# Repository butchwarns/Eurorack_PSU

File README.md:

# Eurorack PSU

A simple linear adjustable power supply for modular synthesizers in the Eurorack format.  
It's easy to build and outputs more than 1A at +12V, -12V and +5V each.

*Eurorack_PSU v0.1.0*

## Motivation

I designed this power supply for use in my own modular synthesizer projects. Thought i'd share the board with other synth builders.
(Gerber files in the repo can be directly uploaded to your pcb manufacturer of choice. Interactive BOM for easy assembly included.)

## A few words of caution

**DANGER OF DEATH:** Do not attempt to build this project if you do not fully know what you are doing!!!  
The build requires wiring a transformer to mains voltage, which can easily end in a deadly accident if done incorrectly!  

**CAUTION:** This project is not suited for beginners! Use the files in this repository at your own risk!  

<hr style="border:1px solid gray">

If you do know what you are doing and want to build the PSU:

I will do my best to test everything, but the occasional bug might still find its way into the project files. Don't hesitate to report found bugs or share ideas on how to improve the board.

## Project status

The *main* branch of this repository holds the current tested version of the board. All potentially breaking changes will be done on the *develop* branch and the build will be tested before merging. Images in this README do not necessarily show the most recent version of the board, though all images will have version numbers in their title.  

## Tech/framework used

- KiCad

## Features

- For standard +12V, -12V, +5V power (±15V should also be possible by adjusting the potentiometers but was not yet tested).  
- $\approx 1.3A$ per rail (regulators are rated $1.5A$ abolute maximum)
- Three LEDs indicate the rails being powered.
- Little heat generation
- Fuses on both secondary windings

Designed to work with the [Eurorack_Bus_Board](https://github.com/butchwarns/Eurorack_Bus_Board/), but can also be used in conjunction with other bus boards.

## Installation

M3 screws and PCB spacers can be used to mount the board to the back of a case.  
Regular 6.3mm flat connectors are used for connecting to both transformer and bus board.  

Use a toroidal transformer with split secondaries at 15VAC and choose one capable of driving enough current to meet your needs!  
(Both positive rails are powered by the same transformer winding.)

## How to use?

Both secondary windings of the transformer are connected on one side of the board. Eurorack power is output on the other side.  
Use a voltmeter to adjust the individual voltages by turning the trimmer potentiometers. if you wan't to be extra precise you can attach a suitable load resistance and adjust the voltages when drawing the same amount of current your modules would do.

## How to build?

Upload the *.zip* in the `gerber_files/` folder to your PCB manufacturer's website to order.

An interactive HTML BOM is available in the `bom/` folder. Just open it in a browser and tick off sourced/placed components.  
Also shows where on the board components should be placed.  

**HINT:** Use good quality solder/flux and clean the board thoroughly after soldering!  

## Component availability/choices

No unobtainium in this project. All components should be easily sourced, at least in europe.  
Feel free to recommend more easily available parts if you can think of any worth replacing.

## Contact

Any questions?   

🡢 contact[at]butchwarns.de

## License

*(TODO: Find appropriate open-hardware license!)*

> Until otherwise stated here, the project is default licensed as proprietary.

Build as many of these boards as you want for personal use, but please make it obvious if your build has modified the project files in any way to avoid confusion!  

My name and any logo of mine that might be present on the board design are copyrighted and are not free to use.

You are free to share the images in the `pictures/` folder of this repository with correct attribution or a link to the project.  

Copr. 2021, Butch Warns

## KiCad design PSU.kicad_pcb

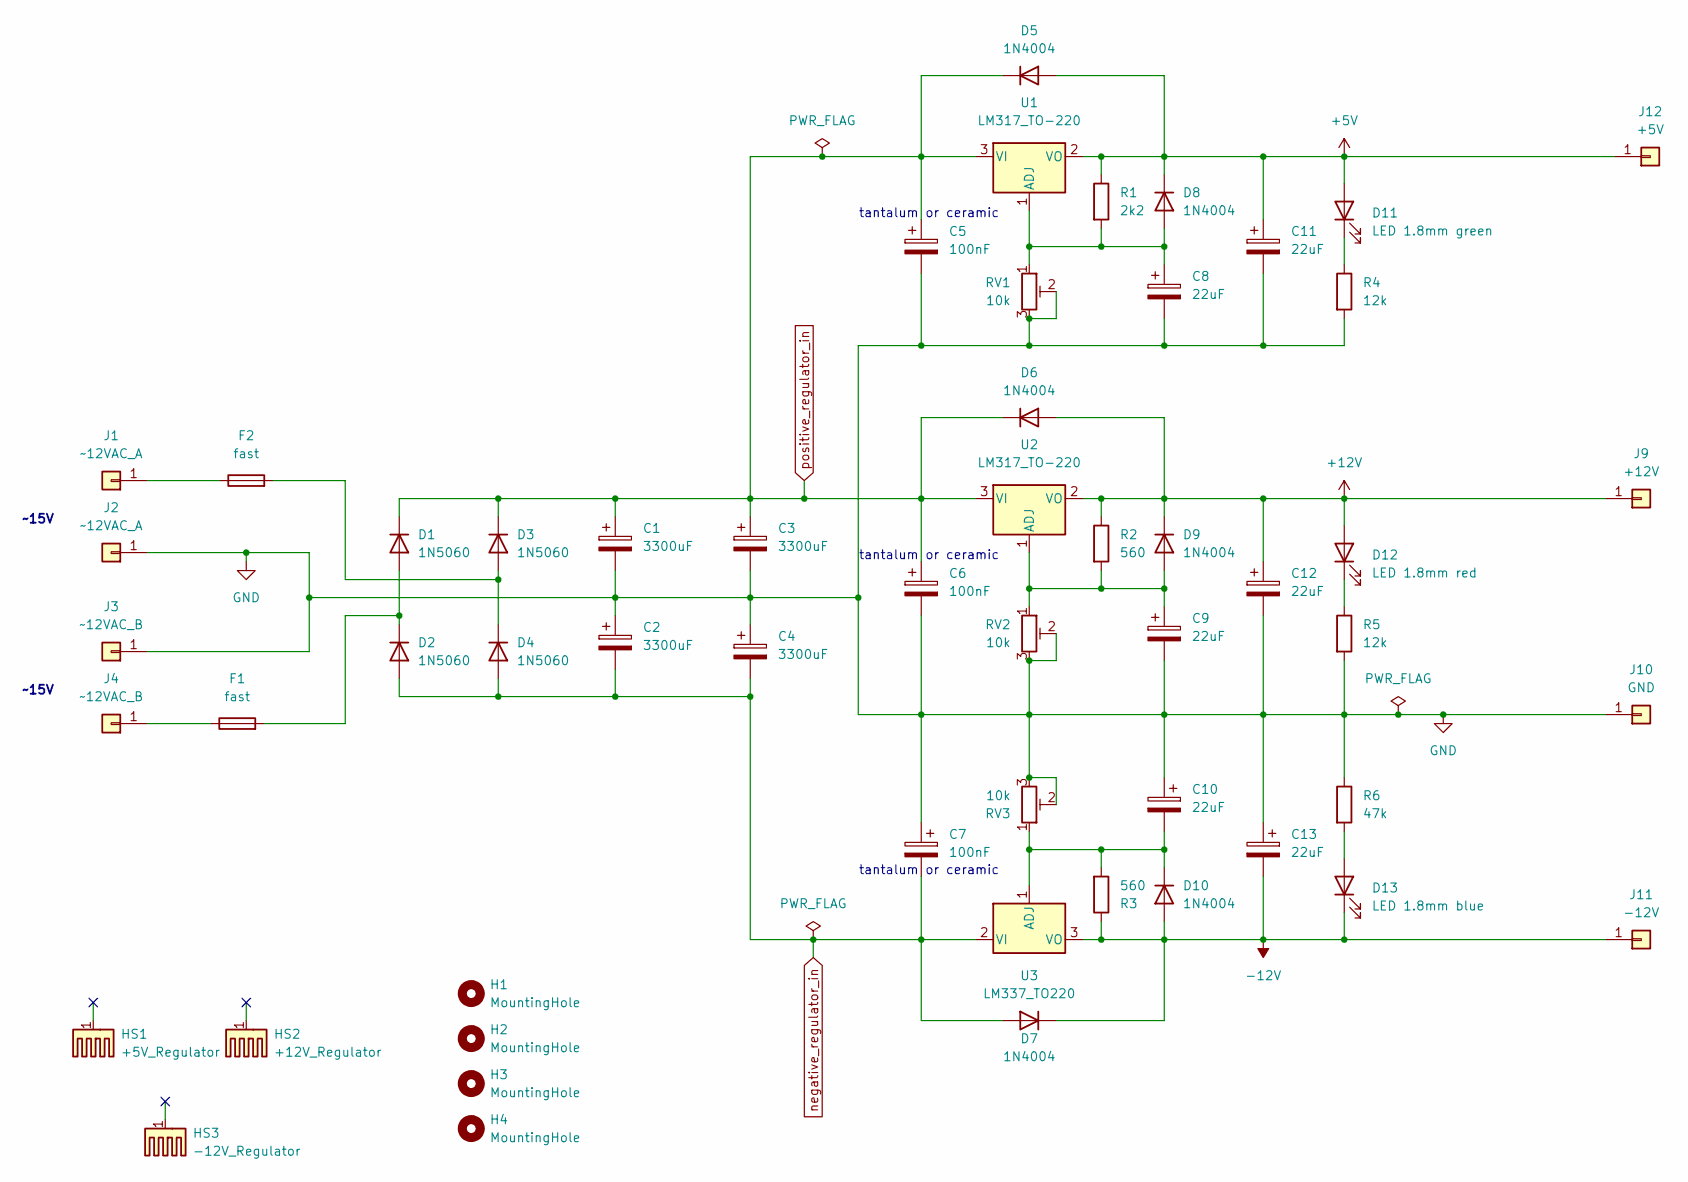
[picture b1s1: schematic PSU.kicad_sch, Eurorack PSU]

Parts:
C1, C2, C3, C4: 3300uF; CP_Radial_D16.0mm_P7.50mm
C5, C6, C7: 100nF; C_Disc_D3.0mm_W1.6mm_P2.50mm
C8, C9, C10, C11, C12, C13: 22uF; CP_Radial_D5.0mm_P2.00mm
D1, D2, D3, D4: 1N5060; D_DO-15_P10.16mm_Horizontal
D5, D6, D7, D8, D9, D10: 1N4004; D_DO-41_SOD81_P10.16mm_Horizontal
D11: LED 1.8mm green; LED_D3.0mm
D12: LED 1.8mm red; LED_D3.0mm
D13: LED 1.8mm blue; LED_D3.0mm
F1, F2: fast; Fuseholder_Cylinder-5x20mm_Schurter_0031_8201_Horizontal_Op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
H1, H2, H3, H4: MountingHole; MountingHole_3.2mm_M3
HS1: +5V_Regulator; Heatsink_Fischer_SK129-STS_42x25mm_2xDrill2.5mm
HS2: +12V_Regulator; Heatsink_Fischer_SK129-STS_42x25mm_2xDrill2.5mm
HS3: -12V_Regulator; Heatsink_Fischer_SK129-STS_42x25mm_2xDrill2.5mm
J1, J2: ~12VAC_A; Flat_Connector_Vogt_6.35mm_P5mm
J3, J4: ~12VAC_B; Flat_Connector_Vogt_6.35mm_P5mm
J9: +12V; Flat_Connector_Vogt_6.35mm_P5mm
J10: GND; Flat_Connector_Vogt_6.35mm_P5mm
J11: -12V; Flat_Connector_Vogt_6.35mm_P5mm
J12: +5V; Flat_Connector_Vogt_6.35mm_P5mm
R1: 2k2; R_Axial_DIN0207_L6.3mm_D2.5mm_P7.62mm_Horizontal
R2, R3: 560; R_Axial_DIN0207_L6.3mm_D2.5mm_P7.62mm_Horizontal
R4, R5: 12k; R_Axial_DIN0207_L6.3mm_D2.5mm_P7.62mm_Horizontal
R6: 47k; R_Axial_DIN0207_L6.3mm_D2.5mm_P7.62mm_Horizontal
RV1, RV2, RV3: 10k; Potentiometer_Bourns_3296W_Vertical
U1, U2: LM317_TO-220; TO-220-3_Vertical
U3: LM337_TO220; TO-220-3_Vertical

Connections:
+5V: C11.1, D5.2 (A), D8.1 (K), D11.2 (A), J12.1, R1.1, U1.2 (VO)
+12V: C12.1, D6.2 (A), D9.1 (K), D12.2 (A), J9.1, R2.1, U2.2 (VO)
-12V: C13.2, D7.1 (K), D10.2 (A), D13.1 (K), J11.1, R3.1, U3.3 (VO)
GND: C1.2, C2.1, C3.2, C4.1, C5.2, C6.2, C7.1, C8.2, C9.2, C10.1, C11.2, C12.2, C13.1, J2.1, J3.1, J10.1, R4.2, R5.2, R6.1, RV1.2, RV1.3, RV2.2, RV2.3, RV3.2, RV3.3
unnamed: C8.1, D8.2 (A), R1.2, RV1.1, U1.1 (ADJ)
unnamed: C9.1, D9.2 (A), R2.2, RV2.1, U2.1 (ADJ)
unnamed: C10.2, D10.1 (K), R3.2, RV3.1, U3.1 (ADJ)
unnamed: D1.2 (A), D2.1 (K), F1.2
unnamed: D3.2 (A), D4.1 (K), F2.2
unnamed: D11.1 (K), R4.1
unnamed: D12.1 (K), R5.1
unnamed: D13.2 (A), R6.2
unnamed: F1.1, J4.1
unnamed: F2.1, J1.1
negative_regulator_in: C2.2, C4.2, C7.2, D2.2 (A), D4.2 (A), D7.2 (A), U3.2 (VI)
positive_regulator_in: C1.1, C3.1, C5.1, C6.1, D1.1 (K), D3.1 (K), D5.1 (K), D6.1 (K), U1.3 (VI), U2.3 (VI)

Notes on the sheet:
tantalum or ceramic
~15V

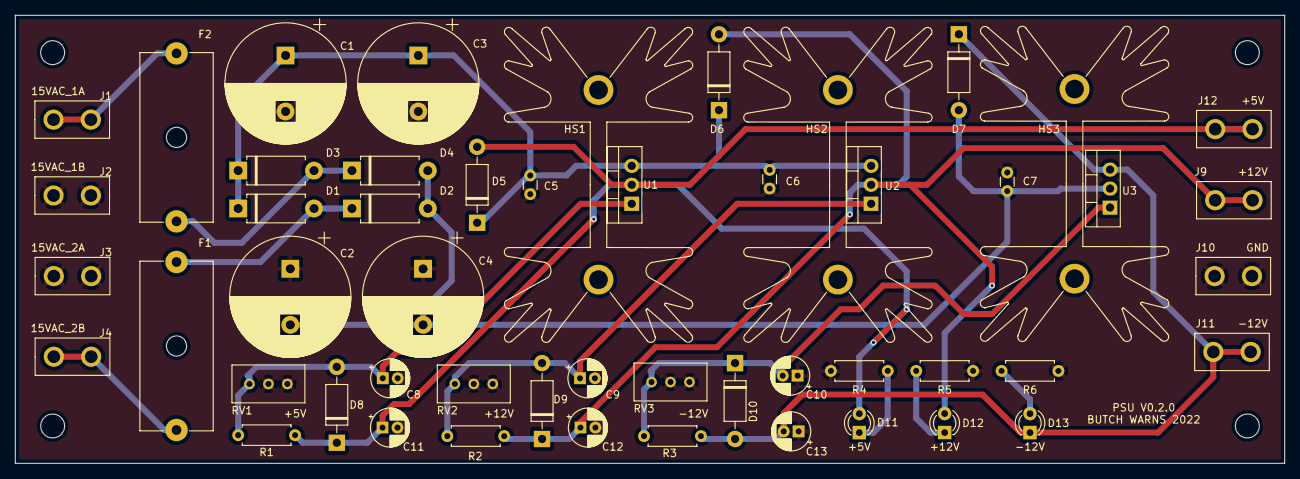
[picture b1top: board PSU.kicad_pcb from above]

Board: 2 copper layers, 170.0 x 60.0 mm, 55 parts (0 on the bottom side), 16 nets.

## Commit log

2022-01-28 Initial commit. PSU v0.1.0.
2022-01-31 Swap rectifier diodes for larger ones. Change input terminal text to be more legible.
2022-05-15 Edit input label text
    Change input labels for improved legibility
2022-05-15 Add jlcpcb order number on bottom layer
2022-05-15 Edit heatsink footprints to show Fischer 3d models
2022-06-03 Add photos of an assembled unit and the bare pcb (both v0.1.0)
2022-06-04 Update README.md
    Start writing actual README
2022-06-05 Do some small touches before making repo public
    Add v010 Gerber files. Add interactive HTML BOM. Set values for LED
    current limiting resistors.
2022-06-05 Update README.md
    Add reference to the Eurorack_Bus_Board and clean README.md
2022-06-05 Write "How to use?" section of README.md
2022-06-10 Add schematic pdf
2022-06-23 Update README.md
    Add TODO
2022-06-29 Update README.md
    Add "open source" badge and change physical units from LaTeX to plain text.
2022-11-06 Update README.md
    typo
